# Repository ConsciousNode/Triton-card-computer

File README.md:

# Triton-card-computer
A ConsciousNode SoftWorks approach to Balanced Ternary Computing hardware.

A balanced-ternary computer built from stock discrete logic: six cards on a backplane, meant to run
[Triton 4](https://github.com/ConsciousNode/Triton) and TritOS Desktop. Every card is specified as a
chip-by-chip netlist and checked cycle by cycle against a reference microcode simulator, which is itself checked
against the Triton emulator.

**Status (2026-11-24):** simulated as a whole machine, and five of the six boards are laid out and routed.
- **The whole machine runs in simulation.** All six cards, joined through the backplane, run in lockstep with the
  reference microsim. It boots and prints `POOP OK`, runs real programs, traps and user mode, and drives every
  device: console, timer and clock, SD card, PS/2 keyboard and mouse, and Video, down to a whole VGA frame captured
  at the DAC. The KERK front panel (run, stop, single-step by instruction or microcycle) is drawn and tested.
  Details are in `INTEGRATION-PLAN.md`.
- **Every card is a real KiCad board** (6U, six layers). Registers, I/O, ALU, Video and Control are autorouted
  with 0 unconnected pads and 0 copper errors in KiCad's checker. **Memory** (241 chips, two-sided) is the
  biggest: it was routing on Kham's laptop on 2026-11-24, after cloud runs kept being cut short. Details and
  pictures are in `kicad/KICAD.md`.
- **JPUSB**, the discrete-logic USB card from [Bare-USB](https://github.com/ConsciousNode/Bare-USB), is translated
  into this repo's part library and cross-checked net by net against its own simulator (`jpusb/`).
- **Not yet:** pinouts and land patterns still need a final check against datasheets, some chips on the table-loading
  path aren't on the boards yet, and nothing has been built on a bench.

*The Control card ("Ed"): 129 chips on both faces, autorouted on six layers.*

## What "ternary" means here
- **Trits are dual-rail:** each trit travels on two binary wires (+ and −), and one of the four combinations is
  never used. That's the same trick Setun used with pairs of ferrite cores, and the same as most ternary hardware
  ever built. Truly three-level devices are still a research frontier.
- **The ternary is in the machine's structure, not in a program.** Arithmetic and decoding are done by wiring and
  by lookup tables held in SRAM. There's **no microcontroller, no FPGA, and no firmware** pretending to be ternary
  anywhere in the machine. Binary parts are used the way Setun used them, as building blocks.
- You can put a probe on a register's two wires and read a trit.

## The cards
Named after the ConsciousNode crew:

| Card | Name | Job |
| --- | --- | --- |
| I/O | Kehai | serial console, timer and real-time clock, SD card, keyboard, ports |
| Video | Komo | framebuffer and display scan-out |
| ALU | Testsuo | arithmetic, shifts, flags |
| Registers | Ren | register file |
| Control | Ed | microsequencer and control store |
| Memory | Vael | main memory |

Front panel: the **KERK panel**. The boot self-test is the **Power On Operational Precheck**; a good boot prints `POOP OK`.

## Layout
- `cards/`: each card's netlist (`*-card.js`), its tables, and its test against the microsim (`*-card-test.js`).
  `netlist.js` and `parts.js` are the part-level simulator; parts carry real part numbers (see `PARTS.md`).
- `microsim/`: the reference microcode simulator, ROMs and bare-metal drivers.
- `integration/`: the backplane check (reads every card's netlist at once) and its findings.
- `roms/`: control-store and table images.
- `kicad/`: the board pipeline (netlist to placed, autorouted `.kicad_pcb`), routed boards and renders in `out/`,
  and `KICAD.md`, the log of how each board was routed.
- `jpusb/`: the JPUSB card brought into the part library, and its cross-check.
- `handheld/`: early ideas for a ternary handheld.
- `TRITONE-CASSETTE.md`: Tritone, a sketch for a ternary cassette drive (three tones, one per trit).
- `NOTES.md`: the working log, kept as written, including superseded plans.
- Design docs: `BACKPLANE-PINOUT.md`, `CONTROL-SIGNALS.md`, `INTEGRATION-PLAN.md`, `PARTS.md`, `TIMING-BUDGET.md`,
  `SHIFTER.md`, `TRITON-4-STORAGE-TIME.md`, `PRIOR-ART.md`, `PCB-PRICING-RECON-testsuo.md`.

## Running the tests
Needs Node.js and a checkout of [ConsciousNode/Triton](https://github.com/ConsciousNode/Triton) next to this repo
(`../Triton`), or set `TRITON_DIR`. The tests compare each card against the Triton reference.

```
cd cards
node alu-card-test.js directed
node control-card-test.js directed
node io-ports-test.js console
```

Each test also has deliberately broken variants ("mutants") that the test must catch.

## Prior art and neighbors
- **Setun** (Moscow State University, 1958) and **Setun-70**: the ternary machines this design descends from.
- **5500FP** by Claudio Lorenzo La Rosa: a 24-trit balanced-ternary RISC processor on an FPGA (2026). It's the
  modern, fast path; this repo is the fixed-discrete-hardware path. Different answers, both worth having. (Our own
  rule for this machine and anything after it: no FPGA and no emulation. The road past discrete chips is a cost-down
  and, someday, a real ternary ASIC.)
- See `PRIOR-ART.md` for more.

## License
MIT, see `LICENSE`.

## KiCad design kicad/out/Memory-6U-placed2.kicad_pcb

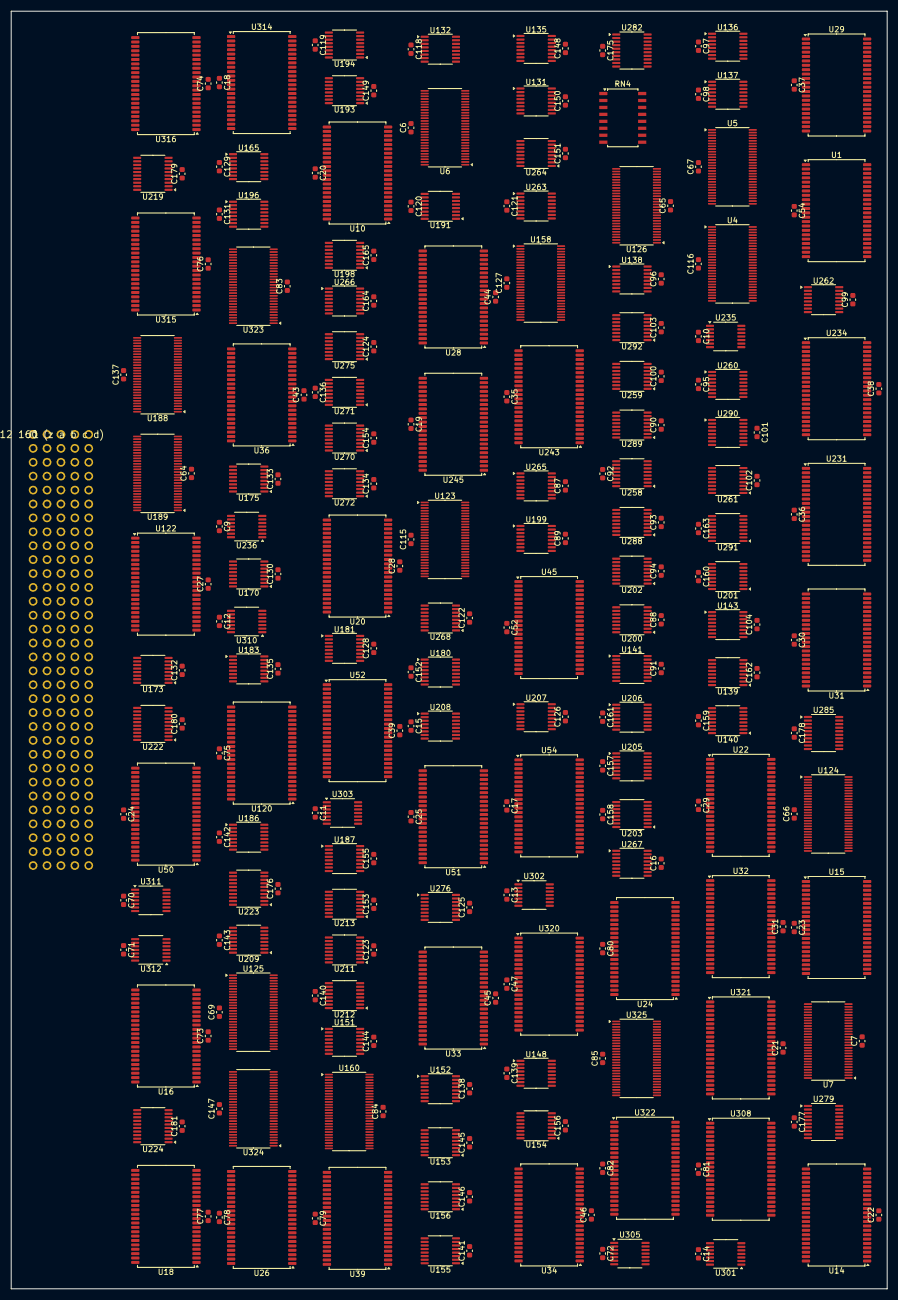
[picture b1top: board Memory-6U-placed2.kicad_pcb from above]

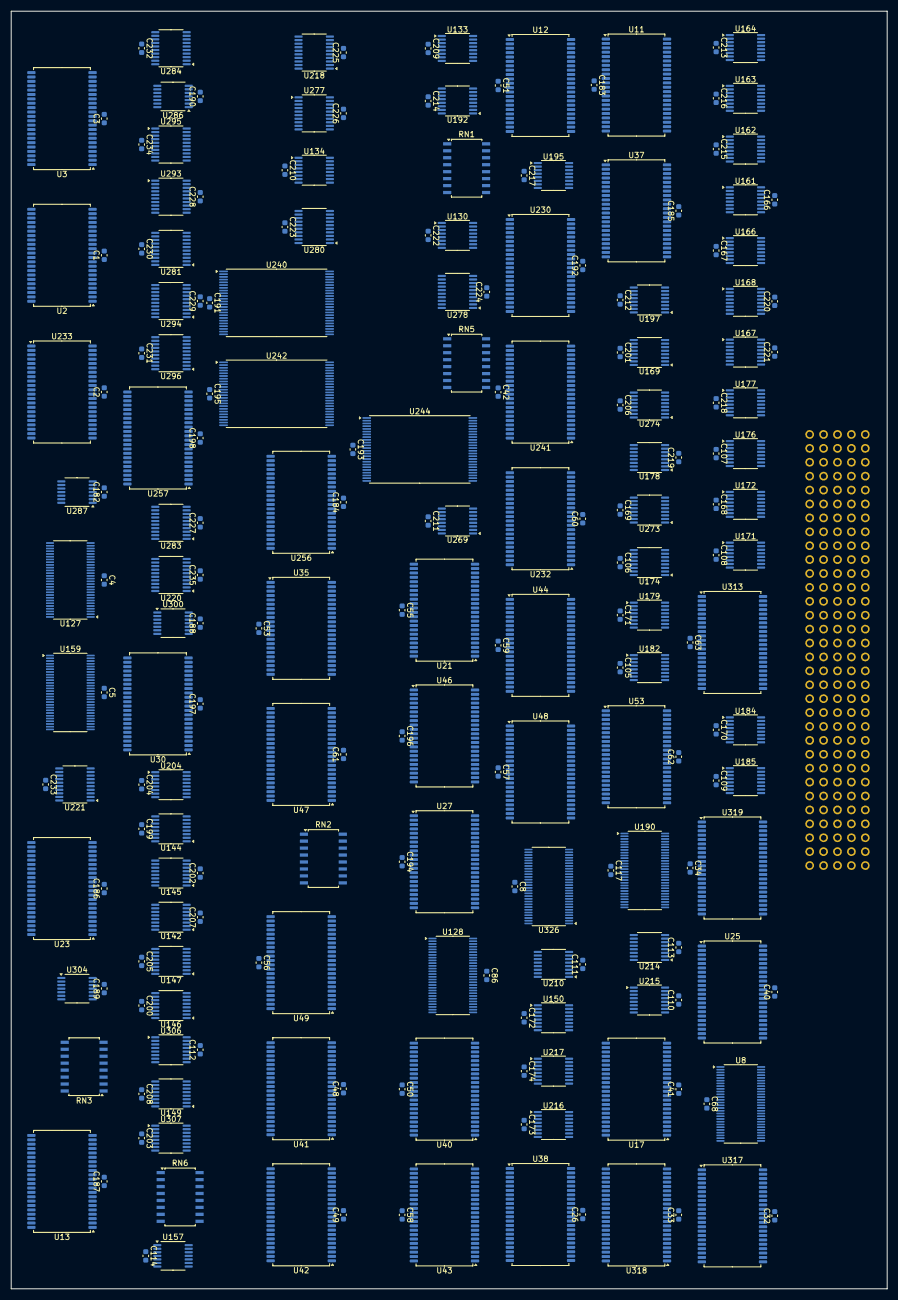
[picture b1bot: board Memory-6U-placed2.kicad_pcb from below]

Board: 4 copper layers, 160.0 x 233.3 mm, 477 parts (211 on the bottom side), 1061 nets, no tracks yet.

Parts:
C1, C2, C3, C4, C5, C6, C7, C8, C9, C10, C11, C12, C13, C14, C15, C16, C17, C18, C19, C20, C21, C22, C23, C24, C25, C26, C27, C28, C29, C30, C31, C32, C33, C34, C35, C36, C37, C38, C39, C40, C41, C42, C43, C44, C45, C46, C47, C48, C49, C50, C51, C52, C53, C54, C55, C56, C57, C58, C59, C60, C61, C62, C63, C64, C65, C66, C67, C68, C69, C70, C71, C72, C73, C74, C75, C76, C77, C78, C79, C80, C81, C82, C83, C84, C85, C86, C87, C88, C89, C90, C91, C92, C93, C94, C95, C96, C97, C98, C99, C100, C101, C102, C103, C104, C105, C106, C107, C108, C109, C110, C111, C112, C113, C114, C115, C116, C117, C118, C119, C120, C121, C122, C123, C124, C125, C126, C127, C128, C129, C130, C131, C132, C133, C134, C135, C136, C137, C138, C139, C140, C141, C142, C143, C144, C145, C146, C147, C148, C149, C150, C151, C152, C153, C154, C155, C156, C157, C158, C159, C160, C161, C162, C163, C164, C165, C166, C167, C168, C169, C170, C171, C172, C173, C174, C175, C176, C177, C178, C179, C180, C181, C182, C183, C184, C185, C186, C187, C188, C189, C190, C191, C192, C193, C194, C195, C196, C197, C198, C199, C200, C201, C202, C203, C204, C205, C206, C207, C208, C209, C210, C211, C212, C213, C214, C215, C216, C217, C218, C219, C220, C221, C222, C223, C224, C225, C226, C227, C228, C229, C230, C231, C232, C233, C234, C235: 100n; C_0603_1608Metric
J1: DIN41612 160 (z a b c d)
RN1, RN2, RN3: RPACK8; SOIC-16W_5.3x10.2mm_P1.27mm
RN4, RN5, RN6: RPACK8G; SOIC-16W_5.3x10.2mm_P1.27mm
U1, U2, U3, U10, U11, U12, U13, U14, U15, U16, U17, U18, U20, U21, U22, U23, U24, U25, U26, U27, U28, U29, U30, U31, U32, U33, U34, U35, U36, U37, U38, U39, U40, U41, U42, U43, U44, U45, U46, U47, U48, U49, U50, U51, U52, U53, U54, U120, U122, U230, U231, U232, U233, U234, U308, U313, U314, U315, U316, U317, U318, U319, U320, U321, U322: IS61WV5128; TSOP-II-44_10.16x18.41mm_P0.8mm
U4, U5, U6, U7, U8, U123, U124, U125, U126, U127, U128, U158, U159, U160, U188, U189, U190, U323, U324, U325, U326: ALVCH16823; TSSOP-56_6.1x14mm_P0.5mm
U130, U131, U132, U133, U134, U135, U136, U137, U138, U139, U140, U141, U142, U143, U144, U145, U146, U147, U148, U149, U150, U151, U152, U153, U154, U155, U156, U161, U162, U163, U164, U165, U166, U167, U168, U169, U170, U171, U172, U173, U174, U175, U176, U177, U178, U179, U180, U181, U182, U183, U184, U185, U186, U187, U268, U269, U270, U271, U272, U273, U274, U275, U276: LVC153; TSSOP-16_4.4x5mm_P0.65mm
U157, U235: LVC04; TSSOP-14_4.4x5mm_P0.65mm
U191, U192, U193, U194, U195, U196, U197, U198, U199, U200, U201, U202, U203, U204, U205, U206, U207, U208, U209, U210, U211, U212, U213, U214, U215, U216, U217: CBTLV3253; TSSOP-16_4.4x5mm_P0.65mm
U218, U219, U220, U221, U222, U223, U224, U277, U278, U279, U280, U281, U282, U283, U293, U294, U295, U296: LVC245; TSSOP-20_4.4x6.5mm_P0.65mm
U236, U287: LVC32; TSSOP-14_4.4x5mm_P0.65mm
U240, U242, U244: IS61WV204816; TSOP-I-48_18.4x12mm_P0.5mm
U241, U243, U245: IS61WV20488; TSOP-II-44_10.16x18.41mm_P0.8mm
U256, U257: IS61WV51216; TSOP-II-44_10.16x18.41mm_P0.8mm
U258, U259, U260, U261, U262: CBTLV3257; TSSOP-16_4.4x5mm_P0.65mm
U263, U264, U265, U266, U267, U288, U289, U290, U291, U292, U306, U307: LVC157; TSSOP-16_4.4x5mm_P0.65mm
U284, U285: LVC574; TSSOP-20_4.4x6.5mm_P0.65mm
U286: LVC08; TSSOP-14_4.4x5mm_P0.65mm
U300, U301, U302, U303, U304, U305, U310, U311, U312: LVC11; TSSOP-14_4.4x5mm_P0.65mm

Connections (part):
+3V3: C1.1, C2.1, C3.1, C4.1, C5.1, C6.1, C7.1, C8.1, C9.1, C10.1, C11.1, C12.1, C13.1, C14.1, C15.1, C16.1, C17.1, C18.1, C19.1, C20.1, C21.1, C22.1, C23.1, C24.1, C25.1, C26.1, C27.1, C28.1, C29.1, C30.1, C31.1, C32.1, C33.1, C34.1, C35.1, C36.1, C37.1, C38.1, C39.1, C40.1, C41.1, C42.1, C43.1, C44.1, C45.1, C46.1, C47.1, C48.1, C49.1, C50.1, C51.1, C52.1, C53.1, C54.1, C55.1, C56.1, C57.1, C58.1, C59.1, C60.1, C61.1, C62.1, C63.1, C64.1, C65.1, C66.1, C67.1, C68.1, C69.1, C70.1, C71.1, C72.1, C73.1, C74.1, C75.1, C76.1, C77.1, C78.1, C79.1, C80.1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
+5V: J1.z8, J1.z16, J1.z24, J1.z32
/CE0: U234.9, U240.7, U241.8
/CE1: U234.10, U242.7, U243.8
/CE2: U234.14, U244.7, U245.8
/FALD: U157.2, U158.30, U158.55, U159.30, U159.55, U160.30, U160.55
/RWE: U236.6, U240.18, U241.15, U242.18, U243.15, U244.18, U245.15
/SWR: U235.11, U286.2, U286.5, U293.19, U294.19, U295.19, U296.19
/UBLD: U122.35, U123.30, U123.55, U124.30, U124.55, U125.30, U125.55
/ULLD: U122.36, U126.30, U126.55, U127.30, U127.55, U128.30, U128.55, U323.30, U323.55, U324.30, U324.55, U325.30, U325.55, U326.30, U326.55
/VSWE: U257.17, U286.6
/VWE: U235.3, U236.8, U282.19, U283.19, U286.1, U286.4
/VXWE: U256.17, U286.3
/WA: U236.3, U236.9, U236.12
/WAS: U236.4, U236.11
/WSTB: J1.d1, U236.13
ABORT: J1.c15, U6.30, U6.55, U7.30, U7.55, U8.30, U8.55, U120.36, U122.3, U157.1, U188.30, U188.55, U189.30, U189.55, U190.30, U190.55, U236.2
BADADDR: J1.d2, U120.14
CLK: J1.c10, U4.29, U4.56, U5.29, U5.56, U6.29, U6.56, U7.29, U7.56, U8.29, U8.56, U123.29, U123.56, U124.29, U124.56, U125.29, U125.56, U126.29, U126.56, U127.29, U127.56, U128.29, U128.56, U158.29, U158.56, U159.29, U159.56, U160.29, U160.56, U188.29, U188.56, U189.29, U189.56, U190.29, U190.56, U323.29, U323.56, U324.29, U324.56, U325.29, U325.56, U326.29, U326.56
CSD0: U1.9, U4.54
CSD1: U1.10, U4.52
CSD2: U1.13, U4.51
CSD3: U1.14, U4.49
CSD4: U1.31, U4.48
CSD5: U1.32, U4.47
CSD6: U1.35, U4.45
CSD7: U1.36, U4.44
CSD8: U2.10, U4.43
CSD9: U2.13, U4.42
CSD10: U2.9, U4.41
CSD11: U2.14, U4.40
CSD12: U2.31, U4.38
CSD13: U2.32, U4.37
CSD14: U2.35, U4.36
CSD15: U2.36, U4.34
CSD16: U3.9, U4.33
CSD17: U3.10, U4.31
CSD18: U3.13, U5.54
CSD19: U3.14, U5.52
CSD20: U3.35, U5.51
CSD21: U3.36, U5.49
CW_/MBUSOE: RN3.2, U4.26, U218.19, U219.19, U220.19, U221.19, U222.19, U223.19, U224.19
CW_/MWR: RN3.4, U5.5, U235.1, U236.1, U277.19, U278.19, U279.19, U280.19, U281.19
CW_BS0_0: RN2.4, U4.17, U191.14, U192.14, U193.14, U194.14, U195.14, U196.14, U197.14, U198.14, U199.14
CW_BS0_1: RN2.5, U4.19, U191.2, U192.2, U193.2, U194.2, U195.2, U196.2, U197.2, U198.2, U199.2
CW_BS1_0: RN2.6, U4.20, U200.14, U201.14, U202.14, U203.14, U204.14, U205.14, U206.14, U207.14, U208.14
CW_BS1_1: RN2.7, U4.21, U200.2, U201.2, U202.2, U203.2, U204.2, U205.2, U206.2, U207.2, U208.2
CW_BS2_0: RN2.8, U4.23, U209.14, U210.14, U211.14, U212.14, U213.14, U214.14, U215.14, U216.14, U217.14
CW_BS2_1: RN3.1, U4.24, U209.2, U210.2, U211.2, U212.2, U213.2, U214.2, U215.2, U216.2, U217.2
CW_MARC: RN1.3, U4.6, U10.16, U308.6
CW_MK0: RN2.2, U4.15, U120.16
CW_MK1: RN2.3, U4.16, U120.3
CW_MOP0: RN1.1, U4.3, U10.19, U11.18, U12.19, U13.40, U14.30, U15.18, U16.6, U17.18, U18.18
CW_MOP1: RN1.2, U4.5, U10.17, U11.7, U12.39, U13.41, U14.38, U15.19, U16.5, U17.17, U18.20, U306.1, U307.1
CW_MS0_0: RN1.4, U4.8, U161.14, U162.14, U163.14, U164.14, U165.14, U166.14, U167.14, U168.14, U169.14
CW_MS0_1: RN1.5, U4.9, U161.2, U162.2, U163.2, U164.2, U165.2, U166.2, U167.2, U168.2, U169.2
CW_MS1_0: RN1.6, U4.10, U170.14, U171.14, U172.14, U173.14, U174.14, U175.14, U176.14, U177.14, U178.14
CW_MS1_1: RN1.7, U4.12, U170.2, U171.2, U172.2, U173.2, U174.2, U175.2, U176.2, U177.2, U178.2
CW_MS2_0: RN1.8, U4.13, U179.14, U180.14, U181.14, U182.14, U183.14, U184.14, U185.14, U186.14, U187.14
CW_MS2_1: RN2.1, U4.14, U179.2, U180.2, U181.2, U182.2, U183.2, U184.2, U185.2, U186.2, U187.2
CW_RFWR: RN3.3, U5.3, U122.41
CW_WL0: RN3.5, U5.6, U268.14, U269.14, U270.14, U271.14, U272.14, U273.14, U274.14, U275.14, U276.14
CW_WL1: RN3.6, U5.8, U268.2, U269.2, U270.2, U271.2, U272.2, U273.2, U274.2, U275.2, U276.2
D0+: J1.a1, U10.30, U123.54, U126.54, U161.4, U161.5, U170.4, U179.4, U218.18, U302.9, U313.3, U314.27
D0-: J1.a2, U10.26, U123.52, U126.52, U161.11, U161.12, U170.12, U179.12, U218.17, U313.6, U314.30
D1+: J1.a3, U10.27, U123.51, U126.51, U162.4, U162.5, U171.4, U180.4, U218.16, U302.10, U313.39, U314.28
D1-: J1.a4, U10.28, U123.49, U126.49, U162.11, U162.12, U171.12, U180.12, U218.15, U313.41, U314.29
D2+: J1.a5, U10.38, U123.48, U126.48, U163.4, U163.5, U172.4, U181.4, U218.14, U302.11, U313.16, U314.16
D2-: J1.a6, U10.29, U123.47, U126.47, U163.11, U163.12, U172.12, U181.12, U218.13, U313.40, U314.26
D3+: J1.a7, U11.41, U123.45, U126.45, U164.4, U164.5, U173.4, U182.4, U218.12, U303.1, U315.20
D3-: J1.a9, U11.40, U123.44, U126.44, U164.11, U164.12, U173.12, U182.12, U218.11, U310.1, U315.26
D4+: J1.a10, U11.27, U123.43, U126.43, U165.4, U165.5, U174.4, U183.4, U219.18, U303.2, U315.27
D4-: J1.a11, U11.16, U123.42, U126.42, U165.11, U165.12, U174.12, U183.12, U219.17, U310.2, U315.28
D5+: J1.a12, U11.30, U123.41, U126.41, U166.4, U166.5, U175.4, U184.4, U219.16, U303.13, U315.16
D5-: J1.a13, U11.29, U123.40, U126.40, U166.11, U166.12, U175.12, U184.12, U219.15, U310.13, U315.30
D6+: J1.a14, U12.26, U123.38, U126.38, U167.4, U167.5, U176.4, U185.4, U219.14, U303.3, U316.38
D6-: J1.a15, U12.28, U123.37, U126.37, U167.11, U167.12, U176.12, U185.12, U219.13, U310.3, U316.39
D7+: J1.a17, U12.29, U123.36, U126.36, U168.4, U168.5, U177.4, U186.4, U219.12, U303.4, U316.40
D7-: J1.a18, U12.38, U123.34, U126.34, U168.11, U168.12, U177.12, U186.12, U219.11, U310.4, U316.41
D8+: J1.a19, U12.27, U123.33, U126.33, U169.4, U169.5, U178.4, U187.4, U220.18, U303.5, U316.17
D8-: J1.a20, U12.30, U123.31, U126.31, U169.11, U169.12, U178.12, U187.12, U220.17, U310.5, U316.18
D9+: J1.a21, U13.20, U124.54, U127.54, U170.5, U220.16, U303.9, U317.4
D9-: J1.a22, U13.26, U124.52, U127.52, U170.11, U220.15, U310.9, U317.16
D10+: J1.a23, U13.19, U124.51, U127.51, U171.5, U220.14, U303.10, U317.5
D10-: J1.a25, U13.28, U124.49, U127.49, U171.11, U220.13, U310.10, U317.41
D11+: J1.a26, U13.29, U124.48, U127.48, U172.5, U220.12, U303.11, U317.7
D11-: J1.a27, U13.18, U124.47, U127.47, U172.11, U220.11, U310.11, U317.3
D12+: J1.a28, U14.27, U124.45, U127.45, U173.5, U221.18, U304.1, U318.27
D12-: J1.a29, U14.20, U124.44, U127.44, U173.11, U221.17, U311.1, U318.19
D13+: J1.a30, U14.28, U124.43, U127.43, U174.5, U221.16, U304.2, U318.28
D13-: J1.a31, U14.7, U124.42, U127.42, U174.11, U221.15, U311.2, U318.18
D14+: J1.b1, U14.26, U124.41, U127.41, U175.5, U221.14, U304.13, U318.29
D14-: J1.b2, U14.16, U124.40, U127.40, U175.11, U221.13, U311.13, U318.17
D15+: J1.b3, U15.27, U124.38, U127.38, U176.5, U221.12, U304.3, U319.3
D15-: J1.b4, U15.39, U124.37, U127.37, U176.11, U221.11, U311.3, U319.27
D16+: J1.b5, U15.26, U124.36, U127.36, U177.5, U222.18, U304.4, U319.39
D16-: J1.b6, U15.40, U124.34, U127.34, U177.11, U222.17, U311.4, U319.28
D17+: J1.b7, U15.28, U124.33, U127.33, U178.5, U222.16, U304.5, U319.40
D17-: J1.b9, U15.41, U124.31, U127.31, U178.11, U222.15, U311.5, U319.26
D18+: J1.b10, U16.19, U125.54, U128.54, U179.5, U222.14, U304.9, U320.3
D18-: J1.b11, U16.26, U125.52, U128.52, U179.11, U222.13, U311.9, U320.4
D19+: J1.b12, U16.18, U125.51, U128.51, U180.5, U222.12, U304.10, U320.5
D19-: J1.b13, U16.27, U125.49, U128.49, U180.11, U222.11, U311.10, U320.6
D20+: J1.b14, U16.20, U125.48, U128.48, U181.5, U223.18, U304.11, U320.7
D20-: J1.b15, U16.17, U125.47, U128.47, U181.11, U223.17, U311.11, U320.16
D21+: J1.b17, U17.27, U125.45, U128.45, U182.5, U223.16, U305.1, U321.18
D21-: J1.b18, U17.19, U125.44, U128.44, U182.11, U223.15, U312.1, U321.3
D22+: J1.b19, U17.29, U125.43, U128.43, U183.5, U223.14, U305.2, U321.19
D22-: J1.b20, U17.28, U125.42, U128.42, U183.11, U223.13, U312.2, U321.4
D23+: J1.b21, U17.30, U125.41, U128.41, U184.5, U223.12, U305.13, U321.20
D23-: J1.b22, U17.20, U125.40, U128.40, U184.11, U223.11, U312.13, U321.5
D24+: J1.b23, U18.26, U125.38, U128.38, U185.5, U224.18, U322.3
D24-: J1.b25, U18.27, U125.37, U128.37, U185.11, U224.17, U312.3, U322.4
D25+: J1.b26, U18.28, U125.36, U128.36, U186.5, U224.16, U322.5
D25-: J1.b27, U18.29, U125.34, U128.34, U186.11, U224.15, U312.4, U322.6
D26+: J1.b28, U18.30, U125.33, U128.33, U187.5, U224.14, U322.7
D26-: J1.b29, U18.38, U125.31, U128.31, U187.11, U224.13, U312.5, U322.16
DB1: U313.9, U315.41
DB2: U313.36, U316.3
DB3: U313.14, U317.6
DB4: U313.32, U318.20
DB5: U313.35, U319.41
DB6: U313.13, U320.17
DB7: U313.10, U321.6
DB8: U312.9, U313.31, U322.17
DM0+: U314.9, U323.54
DM0-: U314.10, U323.52
DM1+: U314.13, U323.51
DM1-: U314.14, U323.49
DM2+: U314.31, U323.48
DM2-: U314.32, U323.47
DM3+: U315.9, U323.45
DM3-: U315.10, U323.44
DM4+: U315.13, U323.43
DM4-: U315.14, U323.42
DM5+: U315.35, U323.41
DM5-: U315.36, U323.40
DM6+: U316.10, U323.38
DM6-: U316.13, U323.37
DM7+: U316.35, U323.36
DM7-: U316.14, U323.34
DM8+: U316.36, U323.33
DM8-: U316.9, U323.31
DM9+: U317.9, U324.54
DM9-: U317.10, U324.52
DM10+: U317.13, U324.51
DM10-: U317.14, U324.49
DM11+: U317.35, U324.48
DM11-: U317.36, U324.47
DM12+: U318.9, U324.45
DM12-: U318.10, U324.44
DM13+: U318.13, U324.43
DM13-: U318.14, U324.42
DM14+: U318.31, U324.41
DM14-: U318.32, U324.40
DM15+: U319.9, U324.38
DM15-: U319.10, U324.37
DM16+: U319.13, U324.36
DM16-: U319.14, U324.34
DM17+: U319.31, U324.33
DM17-: U319.32, U324.31
DM18+: U320.32, U325.54
DM18-: U320.31, U325.52
DM19+: U320.36, U325.51
DM19-: U320.35, U325.49
DM20+: U320.13, U325.48
DM20-: U320.14, U325.47
DM21+: U321.10, U325.45
DM21-: U321.9, U325.44
DM22+: U321.13, U325.43
DM22-: U321.14, U325.42
DM23+: U321.31, U325.41
DM23-: U321.32, U325.40
DM24+: U322.9, U325.38
DM24-: U322.10, U325.37
DM25+: U322.31, U325.36
DM25-: U322.32, U325.34
DM26+: U322.35, U325.33
DM26-: U322.36, U325.31
DN1: U310.12, U313.7
DN2: U310.6, U313.5
DN3: U310.8, U313.4
DN4: U311.12, U313.19
DN5: U311.6, U313.26
DN6: U311.8, U313.20
DN7: U312.12, U313.27
DN8: U312.6, U312.10
ES0: U120.9, U130.14, U131.14, U132.14, U133.14, U134.14, U135.14, U136.14, U137.14, U138.14, U139.14, U140.14, U141.14, U142.14, U143.14, U144.14, U145.14, U146.14, U147.14, U148.14, U149.14, U150.14, U151.14, U152.14, U153.14, U154.14, U155.14, U156.14
ES1: U120.10, U130.2, U131.2, U132.2, U133.2, U134.2, U135.2, U136.2, U137.2, U138.2, U139.2, U140.2, U141.2, U142.2, U143.2, U144.2, U145.2, U146.2, U147.2, U148.2, U149.2, U150.2, U151.2, U152.2, U153.2, U154.2, U155.2, U156.2
FA0+: U158.3, U191.4
FA0-: U158.5, U191.12
FA1+: U158.6, U192.4
FA1-: U158.8, U192.12
FA2+: U158.9, U193.4
FA2-: U158.10, U193.12
FA3+: U158.12, U194.4
FA3-: U158.13, U194.12
FA4+: U158.14, U195.4
FA4-: U158.15, U195.12
FA5+: U158.16, U196.4
FA5-: U158.17, U196.12
FA6+: U158.19, U197.4
FA6-: U158.20, U197.12
FA7+: U158.21, U198.4
FA7-: U158.23, U198.12
FA8+: U158.24, U199.4
FA8-: U158.26, U199.12
FA9+: U159.3, U200.4
FA9-: U159.5, U200.12
FA10+: U159.6, U201.4
FA10-: U159.8, U201.12
FA11+: U159.9, U202.4
FA11-: U159.10, U202.12
FA12+: U159.12, U203.4
FA12-: U159.13, U203.12
FA13+: U159.14, U204.4
FA13-: U159.15, U204.12
FA14+: U159.16, U205.4
FA14-: U159.17, U205.12
FA15+: U159.19, U206.4
FA15-: U159.20, U206.12
FA16+: U159.21, U207.4
FA16-: U159.23, U207.12
FA17+: U159.24, U208.4
FA17-: U159.26, U208.12
FA18+: U160.3, U209.4
FA18-: U160.5, U209.12
FA19+: U160.6, U210.4
FA19-: U160.8, U210.12
FA20+: U160.9, U211.4
FA20-: U160.10, U211.12
FA21+: U160.12, U212.4
FA21-: U160.13, U212.12
FA22+: U160.14, U213.4
FA22-: U160.15, U213.12
FA23+: U160.16, U214.4
FA23-: U160.17, U214.12
FA24+: U160.19, U215.4
FA24-: U160.20, U215.12
FA25+: U160.21, U216.4
FA25-: U160.23, U216.12
FA26+: U160.24, U217.4
FA26-: U160.26, U217.12
FBN: U235.6, U236.10
FBSEL: U233.36, U235.5, U236.5, U263.1, U264.1, U265.1, U266.1, U267.1
FK: J1.c17, U120.13
FN0+: U130.7, U158.54
FN0-: U130.9, U158.52
FN1+: U131.7, U158.51
FN1-: U131.9, U158.49
FN2+: U132.7, U158.48
FN2-: U132.9, U158.47
FN3+: U133.7, U158.45
FN3-: U133.9, U158.44
FN4+: U134.7, U158.43
FN4-: U134.9, U158.42
FN5+: U135.7, U158.41
FN5-: U135.9, U158.40
FN6+: U136.7, U158.38
FN6-: U136.9, U158.37
FN7+: U137.7, U158.36
FN7-: U137.9, U158.34
FN8+: U138.7, U158.33
FN8-: U138.9, U158.31
FN9+: U139.7, U159.54
FN9-: U139.9, U159.52
FN10+: U140.7, U159.51
FN10-: U140.9, U159.49
FN11+: U141.7, U159.48
FN11-: U141.9, U159.47
FN12+: U142.7, U159.45
FN12-: U142.9, U159.44
FN13+: U143.7, U159.43
FN13-: U143.9, U159.42
FN14+: U144.7, U159.41
FN14-: U144.9, U159.40
FN15+: U145.7, U159.38
FN15-: U145.9, U159.37
FN16+: U146.7, U159.36
FN16-: U146.9, U159.34
FN17+: U147.7, U159.33
FN17-: U147.9, U159.31
FN18+: U148.7, U160.54
FN18-: U148.9, U160.52
FN19+: U149.7, U160.51
FN19-: U149.9, U160.49
FN20+: U150.7, U160.48
FN20-: U150.9, U160.47
FN21+: U151.7, U160.45
FN21-: U151.9, U160.44
FN22+: U152.7, U160.43
FN22-: U152.9, U160.42
FN23+: U153.7, U160.41
FN23-: U153.9, U160.40
FN24+: U154.7, U160.38
FN24-: U154.9, U160.37
FN25+: U155.7, U160.36
FN25-: U155.9, U160.34
FN26+: U156.7, U160.33
FN26-: U156.9, U160.31
GND: C1.2, C2.2, C3.2, C4.2, C5.2, C6.2, C7.2, C8.2, C9.2, C10.2, C11.2, C12.2, C13.2, C14.2, C15.2, C16.2, C17.2, C18.2, C19.2, C20.2, C21.2, C22.2, C23.2, C24.2, C25.2, C26.2, C27.2, C28.2, C29.2, C30.2, C31.2, C32.2, C33.2, C34.2, C35.2, C36.2, C37.2, C38.2, C39.2, C40.2, C41.2, C42.2, C43.2, C44.2, C45.2, C46.2, C47.2, C48.2, C49.2, C50.2, C51.2, C52.2, C53.2, C54.2, C55.2, C56.2, C57.2, C58.2, C59.2, C60.2, C61.2, C62.2, C63.2, C64.2, C65.2, C66.2, C67.2, C68.2, C69.2, C70.2, C71.2, C72.2, C73.2, C74.2, C75.2, C76.2, C77.2, C78.2, C79.2, C80.2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
K4_0+: U44.13, U52.3
K4_0-: U44.14, U52.39
K4_1+: U46.9, U52.38
K4_1-: U46.36, U52.28
K4_2+: U48.10, U52.16
K4_2-: U48.13, U52.7
K4_3+: U50.13, U52.17
K4_3-: U50.35, U52.18
K5_0+: U44.35, U52.40
K5_0-: U44.31, U52.41
K5_1+: U46.13, U52.29
K5_1-: U46.31, U52.30
K5_2+: U48.9, U52.27
K5_2-: U48.36, U52.26
K5_3+: U50.32, U52.19
K5_3-: U50.31, U52.20
K6_0+: U44.32, U53.41
K6_0-: U44.10, U53.4
K6_1+: U46.14, U53.6
K6_1-: U46.32, U53.5
K6_2+: U48.14, U53.18
K6_2-: U48.35, U53.17
K6_3+: U50.14, U53.26
K6_3-: U50.36, U53.27
K7_0+: U44.36, U53.40
K7_0-: U44.9, U53.3
K7_1+: U46.35, U53.16
K7_1-: U46.10, U53.7
K7_2+: U48.31, U53.20
K7_2-: U48.32, U53.19
K7_3+: U50.10, U53.28
K7_3-: U50.9, U53.29
K8_0+: U45.9, U54.3
K8_0-: U45.10, U54.4
K8_1+: U47.9, U54.38
K8_1-: U47.10, U54.39
K8_2+: U49.9, U54.26
K8_2-: U49.10, U54.27
K8_3+: U51.9, U54.17
K8_3-: U51.10, U54.16
K9_0+: U45.13, U54.5
K9_0-: U45.14, U54.6
K9_1+: U47.13, U54.40
K9_1-: U47.14, U54.41
K9_2+: U49.13, U54.28
K9_2-: U49.14, U54.29
K9_3+: U51.13, U54.18
K9_3-: U51.14, U54.7
MAR0+: U6.3, U10.3, U20.3, U28.17, U36.41, U44.3, U45.40, U130.6, U191.6, U230.3, U232.40, U300.1
MAR0-: U6.5, U10.6, U20.41, U28.30, U36.4, U44.5, U45.4, U130.10, U191.10, U230.7, U232.19
MAR1+: U6.6, U10.4, U20.29, U28.27, U36.5, U44.29, U45.39, U131.6, U192.6, U230.4, U232.4, U300.2
MAR1-: U6.8, U10.18, U20.30, U28.38, U36.16, U44.30, U45.7, U131.10, U192.10, U230.5, U232.5
MAR2+: U6.9, U10.5, U20.26, U28.28, U36.7, U44.39, U45.38, U132.6, U193.6, U230.20, U232.6, U300.13
MAR2-: U6.10, U10.20, U20.27, U28.41, U36.3, U44.28, U45.5, U132.10, U193.10, U230.19, U232.16
MAR3+: U6.12, U11.3, U20.4, U28.40, U36.6, U44.41, U45.30, U133.6, U194.6, U230.18, U232.7, U300.3
MAR3-: U6.13, U11.4, U20.28, U28.39, U36.19, U44.38, U45.20, U133.10, U194.10, U230.17, U232.3
MAR4+: U6.14, U11.19, U21.5, U29.26, U37.3, U44.7, U45.6, U134.6, U195.6, U230.6, U232.26, U300.4
MAR4-: U6.15, U11.20, U21.39, U29.27, U37.5, U44.4, U45.18, U134.10, U195.10, U230.41, U232.27
MAR5+: U6.16, U11.28, U21.41, U29.5, U37.38, U44.16, U45.19, U135.6, U196.6, U231.18, U232.28, U300.5
MAR5-: U6.17, U11.26, U21.30, U29.6, U37.30, U44.6, U45.17, U135.10, U196.10, U231.20, U232.29
MAR6+: U6.19, U12.18, U21.40, U29.41, U37.29, U44.40, U45.3, U136.6, U197.6, U231.6, U232.41, U300.9
MAR6-: U6.20, U12.16, U21.29, U29.7, U37.28, U44.17, U45.16, U136.10, U197.10, U231.26, U232.38
MAR7+: U6.21, U12.17, U21.3, U29.28, U37.20, U46.5, U47.19, U137.6, U198.6, U231.16, U232.20, U300.10
MAR7-: U6.23, U12.6, U21.4, U29.16, U37.19, U46.4, U47.20, U137.10, U198.10, U231.3, U232.18
MAR8+: U6.24, U12.5, U22.3, U30.3, U38.4, U46.16, U47.30, U138.6, U199.6, U231.7, U232.39, U300.11
MAR8-: U6.26, U12.7, U22.4, U30.4, U38.6, U46.27, U47.29, U138.10, U199.10, U231.19, U232.30
MAR9+: U7.3, U13.4, U22.41, U30.29, U38.18, U46.38, U47.6, U139.6, U200.6, U231.17, U301.1
MAR9-: U7.5, U13.27, U22.6, U30.20, U38.7, U46.18, U47.39, U139.10, U200.10, U231.5
MAR10+: U7.6, U13.3, U22.40, U30.41, U38.19, U46.7, U47.18, U140.6, U201.6, U233.3, U234.41, U301.2
MAR10-: U7.8, U13.17, U22.18, U30.6, U38.3, U46.30, U47.28, U140.10, U201.10, U233.4, U234.4
MAR11+: U7.9, U13.5, U22.7, U30.5, U38.20, U46.3, U47.27, U141.6, U202.6, U233.5, U234.5, U301.13
MAR11-: U7.10, U13.30, U22.16, U30.17, U38.5, U46.6, U47.26, U141.10, U202.10, U233.6, U234.6
MAR12+: U7.12, U14.39, U23.5, U31.41, U39.3, U46.26, U47.40, U142.6, U203.6, U233.39, U234.7, U301.3
MAR12-: U7.13, U14.17, U23.6, U31.20, U39.19, U46.20, U47.38, U142.10, U203.10, U233.20, U234.16
MAR13+: U7.14, U14.40, U23.40, U31.40, U39.4, U46.17, U47.7, U143.6, U204.6, U233.19, U234.17, U301.4
MAR13-: U7.15, U14.18, U23.38, U31.39, U39.18, U46.19, U47.41, U143.10, U204.10, U233.18, U234.18
MAR14+: U7.16, U14.41, U23.39, U31.4, U39.5, U48.17, U49.29, U144.6, U205.6, U233.17, U234.19, U301.5
MAR14-: U7.17, U14.19, U23.41, U31.3, U39.17, U48.16, U49.30, U144.10, U205.10, U233.16, U234.20
MAR15+: U7.19, U15.16, U23.7, U31.19, U39.6, U48.3, U49.27, U145.6, U206.6, U233.26, U234.26, U301.9
MAR15-: U7.20, U15.7, U23.4, U31.18, U39.20, U48.4, U49.26, U145.10, U206.10, U233.27, U234.27
MAR16+: U7.21, U15.4, U24.3, U32.39, U40.29, U48.5, U49.39, U146.6, U207.6, U301.10
MAR16-: U7.23, U15.5, U24.5, U32.30, U40.30, U48.6, U49.18, U146.10, U207.10
MAR17+: U7.24, U15.6, U24.7, U32.17, U40.38, U48.7, U49.38, U147.6, U208.6, U301.11
MAR17-: U7.26, U15.17, U24.4, U32.28, U40.39, U48.41, U49.16, U147.10, U208.10
MAR18+: U8.3, U16.41, U24.27, U32.4, U40.40, U48.26, U49.17, U148.6, U209.6, U302.1
MAR18-: U8.5, U16.40, U24.30, U32.7, U40.41, U48.27, U49.20, U148.10, U209.10
MAR19+: U8.6, U16.3, U24.29, U32.5, U40.19, U48.28, U49.19, U149.6, U210.6, U302.2
MAR19-: U8.8, U16.39, U24.28, U32.6, U40.20, U48.19, U49.28, U149.10, U210.10
MAR20+: U8.9, U16.7, U25.28, U33.39, U41.17, U48.20, U49.4, U150.6, U211.6, U302.13
MAR20-: U8.10, U16.16, U25.27, U33.7, U41.16, U48.29, U49.3, U150.10, U211.10
MAR21+: U8.12, U17.26, U25.40, U33.30, U41.18, U50.38, U51.3, U151.6, U212.6, U302.3
MAR21-: U8.13, U17.4, U25.26, U33.38, U41.19, U50.39, U51.41, U151.10, U212.10
MAR22+: U8.14, U17.3, U25.20, U33.40, U41.7, U50.41, U51.4, U152.6, U213.6, U302.4
MAR22-: U8.15, U17.5, U25.41, U33.3, U41.6, U50.40, U51.39, U152.10, U213.10
MAR23+: U8.16, U17.7, U25.4, U33.20, U41.3, U50.3, U51.5, U153.6, U214.6, U302.5
MAR23-: U8.17, U17.6, U25.3, U33.41, U41.20, U50.5, U51.6, U153.10, U214.10
MAR24+: U8.19, U18.16, U26.41, U34.3, U42.3, U50.4, U51.38, U154.6, U215.6
MAR24-: U8.20, U18.4, U26.40, U34.4, U42.4, U50.6, U51.40, U154.10, U215.10
MAR25+: U8.21, U18.5, U26.39, U34.5, U42.5, U50.19, U51.27, U155.6, U216.6
MAR25-: U8.23, U18.6, U26.30, U34.6, U42.6, U50.18, U51.26, U155.10, U216.10
MAR26+: U8.24, U18.7, U26.29, U34.7, U42.7, U50.16, U51.29, U156.6, U217.6
MAR26-: U8.26, U18.17, U26.38, U34.16, U42.16, U50.17, U51.28, U156.10, U217.10
MB0+: U191.7, U218.2
MB0-: U191.9, U218.3
MB1+: U192.7, U218.4
MB1-: U192.9, U218.5
MB2+: U193.7, U218.6
MB2-: U193.9, U218.7
MB3+: U194.7, U218.8
MB3-: U194.9, U218.9
MB4+: U195.7, U219.2
MB4-: U195.9, U219.3
MB5+: U196.7, U219.4
MB5-: U196.9, U219.5
MB6+: U197.7, U219.6
MB6-: U197.9, U219.7
MB7+: U198.7, U219.8
MB7-: U198.9, U219.9
MB8+: U199.7, U220.2
MB8-: U199.9, U220.3
MB9+: U200.7, U220.4
MB9-: U200.9, U220.5
MB10+: U201.7, U220.6
MB10-: U201.9, U220.7
MB11+: U202.7, U220.8
MB11-: U202.9, U220.9
MB12+: U203.7, U221.2
MB12-: U203.9, U221.3
MB13+: U204.7, U221.4
MB13-: U204.9, U221.5
MB14+: U205.7, U221.6
MB14-: U205.9, U221.7
MB15+: U206.7, U221.8
MB15-: U206.9, U221.9
MB16+: U207.7, U222.2
MB16-: U207.9, U222.3
MB17+: U208.7, U222.4
MB17-: U208.9, U222.5
MB18+: U209.7, U222.6
MB18-: U209.9, U222.7
MB19+: U210.7, U222.8
MB19-: U210.9, U222.9
MB20+: U211.7, U223.2
MB20-: U211.9, U223.3
MB21+: U212.7, U223.4
MB21-: U212.9, U223.5
MB22+: U213.7, U223.6
MB22-: U213.9, U223.7
MB23+: U214.7, U223.8
MB23-: U214.9, U223.9
MB24+: U215.7, U224.2
MB24-: U215.9, U224.3
MB25+: U216.7, U224.4
MB25-: U216.9, U224.5
MB26+: U217.7, U224.6
MB26-: U217.9, U224.7
MC1: U11.17, U308.9
MC2: U12.20, U308.32
MC3: U13.16, U308.35
MC4: U14.29, U308.31
MC5: U15.20, U308.36
MC6: U16.4, U308.13
MC7: U17.41, U308.10
MC8: U18.19, U308.14
MDN0+: U161.7, U188.54
MDN0-: U161.9, U188.52
MDN1+: U162.7, U188.51
MDN1-: U162.9, U188.49
MDN2+: U163.7, U188.48
MDN2-: U163.9, U188.47
MDN3+: U164.7, U188.45
MDN3-: U164.9, U188.44
MDN4+: U165.7, U188.43
MDN4-: U165.9, U188.42
MDN5+: U166.7, U188.41
MDN5-: U166.9, U188.40
MDN6+: U167.7, U188.38
MDN6-: U167.9, U188.37
MDN7+: U168.7, U188.36
MDN7-: U168.9, U188.34
MDN8+: U169.7, U188.33
MDN8-: U169.9, U188.31
MDN9+: U170.7, U189.54
MDN9-: U170.9, U189.52
MDN10+: U171.7, U189.51
MDN10-: U171.9, U189.49
MDN11+: U172.7, U189.48
MDN11-: U172.9, U189.47
MDN12+: U173.7, U189.45
MDN12-: U173.9, U189.44
MDN13+: U174.7, U189.43
MDN13-: U174.9, U189.42
MDN14+: U175.7, U189.41
MDN14-: U175.9, U189.40
MDN15+: U176.7, U189.38
MDN15-: U176.9, U189.37
MDN16+: U177.7, U189.36
MDN16-: U177.9, U189.34
MDN17+: U178.7, U189.33
MDN17-: U178.9, U189.31
MDN18+: U179.7, U190.54
MDN18-: U179.9, U190.52
MDN19+: U180.7, U190.51
MDN19-: U180.9, U190.49
MDN20+: U181.7, U190.48
MDN20-: U181.9, U190.47
MDN21+: U182.7, U190.45
MDN21-: U182.9, U190.44
MDN22+: U183.7, U190.43
MDN22-: U183.9, U190.42
MDN23+: U184.7, U190.41
MDN23-: U184.9, U190.40
MDN24+: U185.7, U190.38
MDN24-: U185.9, U190.37
MDN25+: U186.7, U190.36
MDN25-: U186.9, U190.34
MDN26+: U187.7, U190.33
MDN26-: U187.9, U190.31
MDR0+: U161.6, U188.3, U191.5, U268.6
MDR0-: U161.10, U188.5, U191.11, U268.10
MDR1+: U162.6, U188.6, U192.5, U269.6
MDR1-: U162.10, U188.8, U192.11, U269.10
MDR2+: U163.6, U188.9, U193.5, U270.6
MDR2-: U163.10, U188.10, U193.11, U270.10
MDR3+: U164.6, U188.12, U194.5, U271.6
MDR3-: U164.10, U188.13, U194.11, U271.10
MDR4+: U165.6, U188.14, U195.5, U272.6
MDR4-: U165.10, U188.15, U195.11, U272.10
MDR5+: U166.6, U188.16, U196.5, U273.6
MDR5-: U166.10, U188.17, U196.11, U273.10
MDR6+: U167.6, U188.19, U197.5, U274.6
MDR6-: U167.10, U188.20, U197.11, U274.10
MDR7+: U168.6, U188.21, U198.5, U275.6
MDR7-: U168.10, U188.23, U198.11, U275.10
MDR8+: U169.6, U188.24, U199.5, U276.6
MDR8-: U169.10, U188.26, U199.11, U276.10
MDR9+: U170.6, U189.3, U200.5, U268.5
MDR9-: U170.10, U189.5, U200.11, U268.11
MDR10+: U171.6, U189.6, U201.5, U269.5
MDR10-: U171.10, U189.8, U201.11, U269.11
MDR11+: U172.6, U189.9, U202.5, U270.5
MDR11-: U172.10, U189.10, U202.11, U270.11
MDR12+: U173.6, U189.12, U203.5, U271.5
MDR12-: U173.10, U189.13, U203.11, U271.11
MDR13+: U174.6, U189.14, U204.5, U272.5
MDR13-: U174.10, U189.15, U204.11, U272.11
MDR14+: U175.6, U189.16, U205.5, U273.5
MDR14-: U175.10, U189.17, U205.11, U273.11
MDR15+: U176.6, U189.19, U206.5, U274.5
MDR15-: U176.10, U189.20, U206.11, U274.11
MDR16+: U177.6, U189.21, U207.5, U275.5
MDR16-: U177.10, U189.23, U207.11, U275.11
MDR17+: U178.6, U189.24, U208.5, U276.5
MDR17-: U178.10, U189.26, U208.11, U276.11
MDR18+: U179.6, U190.3, U209.5, U268.4
MDR18-: U179.10, U190.5, U209.11, U268.12
MDR19+: U180.6, U190.6, U210.5, U269.4
MDR19-: U180.10, U190.8, U210.11, U269.12
MDR20+: U181.6, U190.9, U211.5, U270.4
MDR20-: U181.10, U190.10, U211.11, U270.12
MDR21+: U182.6, U190.12, U212.5, U271.4
MDR21-: U182.10, U190.13, U212.11, U271.12
MDR22+: U183.6, U190.14, U213.5, U272.4
MDR22-: U183.10, U190.15, U213.11, U272.12
MDR23+: U184.6, U190.16, U214.5, U273.4
MDR23-: U184.10, U190.17, U214.11, U273.12
MDR24+: U185.6, U190.19, U215.5, U274.4
MDR24-: U185.10, U190.20, U215.11, U274.12
MDR25+: U186.6, U190.21, U216.5, U275.4
MDR25-: U186.10, U190.23, U216.11, U275.12
MDR26+: U187.6, U190.24, U217.5, U276.4
MDR26-: U187.10, U190.26, U217.11, U276.12
MN0+: U6.54, U10.9
MN0-: U6.52, U10.32
MN1+: U6.51, U10.13
MN1-: U6.49, U10.14
MN2+: U6.48, U10.10
MN2-: U6.47, U10.31
MN3+: U6.45, U11.9
MN3-: U6.44, U11.10
MN4+: U6.43, U11.13
MN4-: U6.42, U11.14
MN5+: U6.41, U11.31
MN5-: U6.40, U11.32
MN6+: U6.38, U12.9
MN6-: U6.37, U12.10
MN7+: U6.36, U12.13
MN7-: U6.34, U12.14
MN8+: U6.33, U12.31
MN8-: U6.31, U12.32
MN9+: U7.54, U13.9
MN9-: U7.52, U13.10
MN10+: U7.51, U13.13
MN10-: U7.49, U13.14
MN11+: U7.48, U13.31
MN11-: U7.47, U13.32
MN12+: U7.45, U14.32
MN12-: U7.44, U14.31
MN13+: U7.43, U14.36
MN13-: U7.42, U14.35
MN14+: U7.41, U14.13
MN14-: U7.40, U14.14
MN15+: U7.38, U15.9
MN15-: U7.37, U15.10
MN16+: U7.36, U15.13
MN16-: U7.34, U15.14
MN17+: U7.33, U15.31
MN17-: U7.31, U15.32
MN18+: U8.54, U16.9
MN18-: U8.52, U16.10
MN19+: U8.51, U16.31
MN19-: U8.49, U16.32
MN20+: U8.48, U16.35
MN20-: U8.47, U16.36
MN21+: U8.45, U17.10
MN21-: U8.44, U17.13
MN22+: U8.43, U17.9
MN22-: U8.42, U17.14
MN23+: U8.41, U17.35
MN23-: U8.40, U17.36
MN24+: U8.38, U18.32
MN24-: U8.37, U18.31
MN25+: U8.36, U18.36
MN25-: U8.34, U18.35
MN26+: U8.33, U18.13
MN26-: U8.31, U18.14
MODE: J1.d23, U120.20, U232.37, U233.28, U234.28, U235.9
MODEN: U231.37, U235.8
MWRH: U235.2, U240.43, U241.37, U242.43, U243.37, U244.43, U245.37, U287.1
N_K4: U52.9, U120.18
N_K5: U52.10, U120.19
N_K6: U53.9, U120.29
N_K7: U53.10, U120.30
N_K8: U54.9, U120.5
N_K9: U54.10, U120.6
N_V1: U27.36, U120.4
N_V2: U35.31, U120.17
N_V3: U43.14, U120.7
PB0: U302.8, U306.3
PB1: U303.12, U306.6
PB2: U303.6, U306.10
PB3: U303.8, U306.13
PB4: U304.12, U307.3
PB5: U304.6, U307.6
PB6: U304.8, U307.10
PB7: U305.12, U307.13
PM0: U300.12, U306.2
PM1: U300.6, U306.5
PM2: U300.8, U306.11
PM3: U301.12, U306.14
PM4: U301.6, U307.2
PM5: U301.8, U307.5
PM6: U302.12, U307.11
PM7: U302.6, U307.14
PRIV: J1.d25, U120.40
PROTEN: J1.d27, U120.27
PS0: U306.4, U308.39
PS1: U306.7, U308.40
PS2: U306.9, U308.3
PS3: U306.12, U308.4
PS4: U307.4, U308.41
PS5: U307.7, U308.38
PS6: U307.9, U308.7
PS7: U307.12, U308.5
RA0: U230.31, U240.5, U241.3, U242.5, U243.3, U244.5, U245.3, U258.3, U288.2
RA1: U230.36, U240.4, U241.4, U242.4, U243.4, U244.4, U245.4, U258.6, U288.5
RA2: U230.35, U240.3, U241.5, U242.3, U243.5, U244.3, U245.5, U258.10, U288.11
RA3: U230.10, U240.2, U241.6, U242.2, U243.6, U244.2, U245.6, U258.13, U288.14
RA4: U230.32, U240.1, U241.7, U242.1, U243.7, U244.1, U245.7, U259.3, U289.2
RA5: U230.9, U240.48, U241.16, U242.48, U243.16, U244.48, U245.16, U259.6, U289.5
RA6: U230.14, U240.47, U241.17, U242.47, U243.17, U244.47, U245.17, U259.10, U289.11
RA7: U230.13, U240.46, U241.18, U242.46, U243.18, U244.46, U245.18, U259.13, U289.14
RA8: U231.9, U232.14, U240.45, U241.19, U242.45, U243.19, U244.45, U245.19, U260.3, U290.2
RA9: U231.10, U232.10, U240.30, U241.20, U242.30, U243.20, U244.30, U245.20, U260.6, U290.5
RA10: U231.36, U232.13, U240.29, U241.26, U242.29, U243.26, U244.29, U245.26, U260.10, U290.11
RA11: U231.35, U232.36, U240.28, U241.27, U242.28, U243.27, U244.28, U245.27, U260.13, U290.14
RA12: U231.14, U232.35, U240.27, U241.28, U242.27, U243.28, U244.27, U245.28, U261.3, U291.2
RA13: U231.31, U232.32, U240.26, U241.29, U242.26, U243.29, U244.26, U245.29, U261.6, U291.5
RA14: U231.13, U232.9, U240.24, U241.30, U242.24, U243.30, U244.24, U245.30, U261.10, U291.11
RA15: U231.32, U232.31, U240.23, U241.38, U242.23, U243.38, U244.23, U245.38, U261.13, U291.14
RA16: U233.10, U240.22, U241.39, U242.22, U243.39, U244.22, U245.39, U262.3, U292.2
RA17: U233.32, U240.21, U241.40, U242.21, U243.40, U244.21, U245.40, U262.6, U292.5
RA18: U233.9, U240.20, U241.41, U242.20, U243.41, U244.20, U245.41, U262.10, U292.11
RA19: U233.31, U240.19, U241.25, U242.19, U243.25, U244.19, U245.25
RA20: U233.35, U240.44, U241.42, U242.44, U243.42, U244.44, U245.42
RAMD0: RN4.1, U240.8, U242.8, U244.8, U263.2, U277.18
RAMD1: RN4.2, U240.9, U242.9, U244.9, U263.5, U277.17
RAMD2: RN4.3, U240.10, U242.10, U244.10, U263.11, U277.16
RAMD3: RN4.4, U240.11, U242.11, U244.11, U263.14, U277.15
RAMD4: RN4.5, U240.14, U242.14, U244.14, U264.2, U277.14
RAMD5: RN4.6, U240.15, U242.15, U244.15, U264.5, U277.13
RAMD6: RN4.7, U240.16, U242.16, U244.16, U264.11, U277.12
RAMD7: RN4.8, U240.17, U242.17, U244.17, U264.14, U277.11
RAMD8: RN5.1, U240.31, U242.31, U244.31, U265.2, U278.18
RAMD9: RN5.2, U240.32, U242.32, U244.32, U265.5, U278.17
RAMD10: RN5.3, U240.33, U242.33, U244.33, U265.11, U278.16
RAMD11: RN5.4, U240.34, U242.34, U244.34, U265.14, U278.15
RAMD12: RN5.5, U240.37, U242.37, U244.37, U266.2, U278.14
RAMD13: RN5.6, U240.38, U242.38, U244.38, U266.5, U278.13
RAMD14: RN5.7, U240.39, U242.39, U244.39, U266.11, U278.12
RAMD15: RN5.8, U240.40, U242.40, U244.40, U266.14, U278.11
RAMD16: RN6.1, U241.9, U243.9, U245.9, U267.2, U279.18
RAMD17: RN6.2, U241.10, U243.10, U245.10, U267.5, U279.17
RD0: U161.3, U170.3, U179.3, U191.3, U263.4
RD1: U161.13, U170.13, U179.13, U191.13, U263.7
RD2: U162.3, U171.3, U180.3, U192.3, U263.9
RD3: U162.13, U171.13, U180.13, U192.13, U263.12
RD4: U163.3, U172.3, U181.3, U193.3, U264.4
RD5: U163.13, U172.13, U181.13, U193.13, U264.7
RD6: U164.3, U173.3, U182.3, U194.3, U264.9
RD7: U164.13, U173.13, U182.13, U194.13, U264.12
RD8: U165.3, U174.3, U183.3, U195.3, U265.4
RD9: U165.13, U174.13, U183.13, U195.13, U265.7
RD10: U166.3, U175.3, U184.3, U196.3, U265.9
RD11: U166.13, U175.13, U184.13, U196.13, U265.12
RD12: U167.3, U176.3, U185.3, U197.3, U266.4
RD13: U167.13, U176.13, U185.13, U197.13, U266.7
RD14: U168.3, U177.3, U186.3, U198.3, U266.9
RD15: U168.13, U177.13, U186.13, U198.13, U266.12
RD16: U169.3, U178.3, U187.3, U199.3, U267.4
RD17: U169.13, U178.13, U187.13, U199.13, U267.7
RESET: J1.c12, U4.2, U4.27, U5.2, U5.27
RSLOT0: J1.d11, U122.17
RSLOT1: J1.d12, U122.4
RSLOT2: J1.d13, U122.5
RSLOT3: J1.d14, U122.6
RSLOT4: J1.d15, U122.7
SA0: U258.2, U288.3
SA1: U258.5, U288.6
SA2: U258.11, U288.10
SA3: U258.14, U288.13
SA4: U259.2, U289.3
SA5: U259.5, U289.6
SA6: U259.11, U289.10
SA7: U259.14, U289.13
SA8: U260.2, U290.3
SA9: U260.5, U290.6
SA10: U260.11, U290.10
SA11: U260.14, U290.13
SA12: U261.2, U291.3
SA13: U261.5, U291.6
SA14: U261.11, U291.10
SA15: U261.14, U291.13
SA16: U262.2, U292.3
SA17: U262.5, U292.6
SA18: U262.11, U292.10
SCLK: J1.c11, U284.11, U285.11
SD0: U257.7, U282.18, U284.2, U295.18
SD1: U257.8, U282.17, U284.3, U295.17
SD2: U257.9, U282.16, U284.4, U295.16
SD3: U257.10, U282.15, U284.5, U295.15
SD4: U257.13, U282.14, U284.6, U295.14
SD5: U257.14, U282.13, U284.7, U295.13
SD6: U257.15, U282.12, U284.8, U295.12
SD7: U257.16, U282.11, U284.9, U295.11
SD8: U257.29, U283.18, U285.2, U296.18
SD9: U257.30, U283.17, U285.3, U296.17
SD10: U257.31, U283.16, U285.4, U296.16
SD11: U257.32, U283.15, U285.5, U296.15
SI0: U293.2, U295.2
SI1: U293.3, U295.3
SI2: U293.4, U295.4
SI3: U293.5, U295.5
SI4: U293.6, U295.6
SI5: U293.7, U295.7
SI6: U293.8, U295.8
SI7: U293.9, U295.9
SI8: U294.2, U296.2
SI9: U294.3, U296.3
SI10: U294.4, U296.4
SI11: U294.5, U296.5
SPRNR: J1.c18, U122.16
SWRH: U235.10, U287.2, U287.5, U288.1, U289.1, U290.1, U291.1, U292.1
UA0: J1.b30, U1.17, U2.28, U3.39
UA1: J1.b31, U1.18, U2.18, U3.5
UA2: J1.c1, U1.19, U2.16, U3.17
UA3: J1.c2, U1.30, U2.27, U3.41
UA4: J1.c3, U1.29, U2.26, U3.40
UA5: J1.c4, U1.4, U2.7, U3.4
UA6: J1.c5, U1.3, U2.6, U3.7
UA7: J1.c6, U1.7, U2.17, U3.16
UA8: J1.c7, U1.20, U2.20, U3.6
UA9: J1.c9, U1.16, U2.19, U3.3
UB0+: U20.19, U123.3
UB0-: U20.20, U123.5
UB1+: U20.5, U123.6
UB1-: U20.6, U123.8
UB2+: U20.7, U123.9
UB2-: U20.18, U123.10
UB3+: U20.17, U123.12
UB3-: U20.16, U123.13
UB4+: U21.16, U123.14
UB4-: U21.19, U123.15
UB5+: U21.17, U123.16
UB5-: U21.26, U123.17
UB6+: U21.18, U123.19
UB6-: U21.20, U123.20
UB7+: U21.7, U123.21
UB7-: U21.6, U123.23
UB8+: U22.17, U123.24
UB8-: U22.5, U123.26
UB9+: U22.39, U124.3
UB9-: U22.38, U124.5
UB10+: U22.27, U124.6
UB10-: U22.28, U124.8
UB11+: U22.29, U124.9
UB11-: U22.30, U124.10
UB12+: U23.18, U124.12
UB12-: U23.16, U124.13
UB13+: U23.26, U124.14
UB13-: U23.19, U124.15
UB14+: U23.17, U124.16
UB14-: U23.27, U124.17
UB15+: U23.28, U124.19
UB15-: U23.20, U124.20
UB16+: U24.19, U124.21
UB16-: U24.17, U124.23
UB17+: U24.20, U124.24
UB17-: U24.18, U124.26
UB18+: U24.40, U125.3
UB18-: U24.38, U125.5
UB19+: U24.39, U125.6
UB19-: U24.41, U125.8
UB20+: U25.7, U125.9
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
